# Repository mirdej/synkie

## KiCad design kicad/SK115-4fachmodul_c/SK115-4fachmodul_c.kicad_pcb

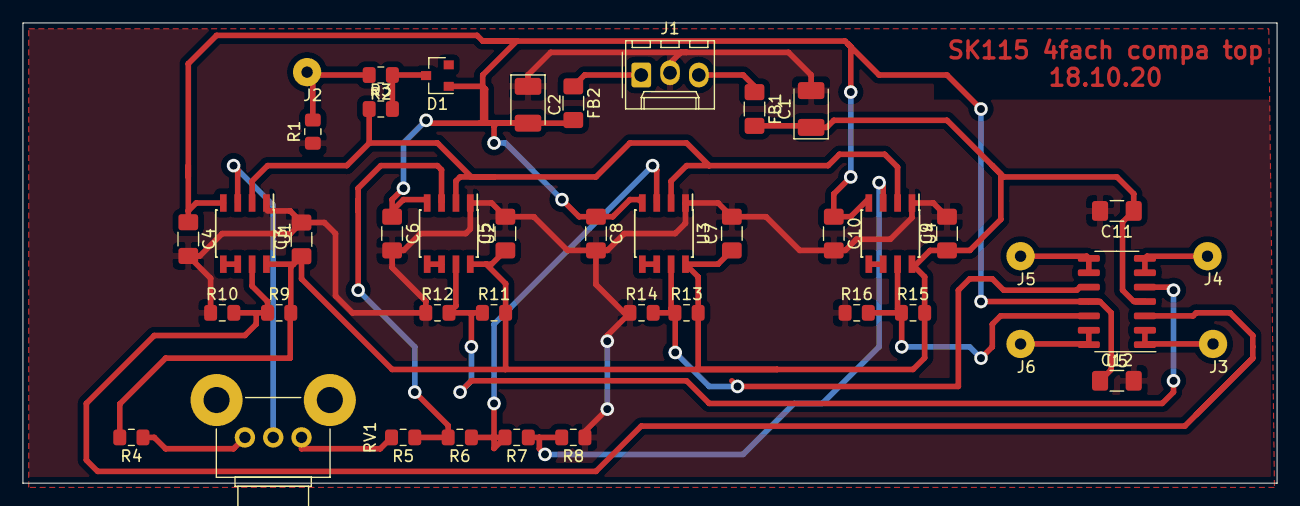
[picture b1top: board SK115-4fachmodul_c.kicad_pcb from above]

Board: 2 copper layers, 110.7 x 40.6 mm, 43 parts (0 on the bottom side), 25 nets.

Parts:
C1, C2: 10u; CP_EIA-3528-21_Kemet-B_Pad1.50x2.35mm_HandSolder
C3, C4, C5, C6, C7, C8, C9, C10, C11, C12: 100n; C_1206_3216Metric_Pad1.42x1.75mm_HandSolder
D1: BAT54S; SOT-23
FB1, FB2: 330u; L_1206_3216Metric_Pad1.42x1.75mm_HandSolder
J1: Power; Molex_KK-254_AE-6410-03A_1x03_P2.54mm_Vertical
J2: SIFF_IN; Solderpad_1mm
J3: CV4; Solderpad_1mm
J4: CV3; Solderpad_1mm
J5: CV2; Solderpad_1mm
J6: CV1; Solderpad_1mm
R1: 4k7; R_0805_2012Metric_Pad1.15x1.40mm_HandSolder
R2, R3: 100; R_0805_2012Metric_Pad1.15x1.40mm_HandSolder
R4: 49k; R_0805_2012Metric_Pad1.15x1.40mm_HandSolder
R5, R6, R7, R8: 2k2; R_0805_2012Metric_Pad1.15x1.40mm_HandSolder
R9, R11, R13, R15: 6k8; R_0805_2012Metric_Pad1.15x1.40mm_HandSolder
R10, R12, R14, R16: 1k8; R_0805_2012Metric_Pad1.15x1.40mm_HandSolder
RV1: 10k; Potentiometer_Alps_RK09K_Single_Horizontal
U1, U2, U3, U4: LM311D; SOIC-8_3.9x4.9mm_P1.27mm
U5: TL074; SOIC-14_3.9x8.7mm_P1.27mm

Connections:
+5V: C1.1, C3.1, C5.1, C7.1, C9.1, C11.1, D1.2, FB1.2, R4.2, R9.2, R11.2, R13.2, R15.2, U1.8, U2.8, U3.8, U4.8, U5.4
-5V: C2.2, C4.1, C6.1, C8.1, C10.1, C12.1, D1.1, FB2.2, U1.4, U2.4, U3.4, U4.4, U5.11
GND: C1.2, C2.1, C3.2, C4.2, C5.2, C6.2, C7.2, C8.2, C9.2, C10.2, C11.2, C12.2, J1.2, R1.1, R8.1, R10.1, R12.1, R14.1, R16.1, U1.1, U2.1, U3.1, U4.1
unnamed: D1.3, R2.1, R3.2
unnamed: FB1.1, J1.3
unnamed: FB2.1, J1.1
unnamed: J2.1, R1.2, R2.2
unnamed: J3.1, U5.1, U5.2
unnamed: J4.1, U5.6, U5.7
unnamed: J5.1, U5.8, U5.9
unnamed: J6.1, U5.13, U5.14
unnamed: R3.1, U1.2, U2.2, U3.2, U4.2
unnamed: R4.1, RV1.1
unnamed: R5.1, R6.2, U2.3
unnamed: R5.2, RV1.2, RV1.3, U1.3
unnamed: R6.1, R7.2, U3.3
unnamed: R7.1, R8.2, U4.3
unnamed: R9.1, R10.2, U1.7, U5.3
unnamed: R11.1, R12.2, U2.7, U5.5
unnamed: R13.1, R14.2, U3.7, U5.10
unnamed: R15.1, R16.2, U4.7, U5.12
unnamed: U1.5, U1.6
unnamed: U2.5, U2.6
unnamed: U3.5, U3.6
unnamed: U4.5, U4.6

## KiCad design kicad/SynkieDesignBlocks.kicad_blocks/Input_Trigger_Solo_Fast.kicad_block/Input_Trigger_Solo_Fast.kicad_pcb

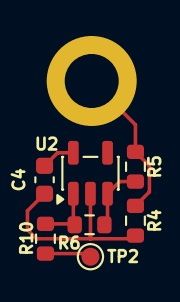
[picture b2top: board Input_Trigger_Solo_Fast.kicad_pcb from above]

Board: 2 copper layers, 8 parts (1 on the bottom side), 6 nets.

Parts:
C4: 100n; C_0603_1608Metric
J3: Clock In; Banana2mm-Löthülse
R4: 12k; R_0603_1608Metric
R5: 2k2; R_0603_1608Metric
R6: 100k; R_0603_1608Metric
R10: 75; R_0603_1608Metric
TP2: Comp2Out; TestPoint_Pad_D1.0mm
U2: TLV3201; SOT-23-5

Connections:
+5V: C4.2, U2.5 (V+)
GND: C4.1, R4.1, U2.2 (V-)
unnamed: J3.1 (Pin_1_1), R4.2, R5.2
unnamed: R6.1, R10.2, U2.1
unnamed: R5.1, R6.2, U2.3 (+)
unnamed: R10.1, TP2.1 (1_1)

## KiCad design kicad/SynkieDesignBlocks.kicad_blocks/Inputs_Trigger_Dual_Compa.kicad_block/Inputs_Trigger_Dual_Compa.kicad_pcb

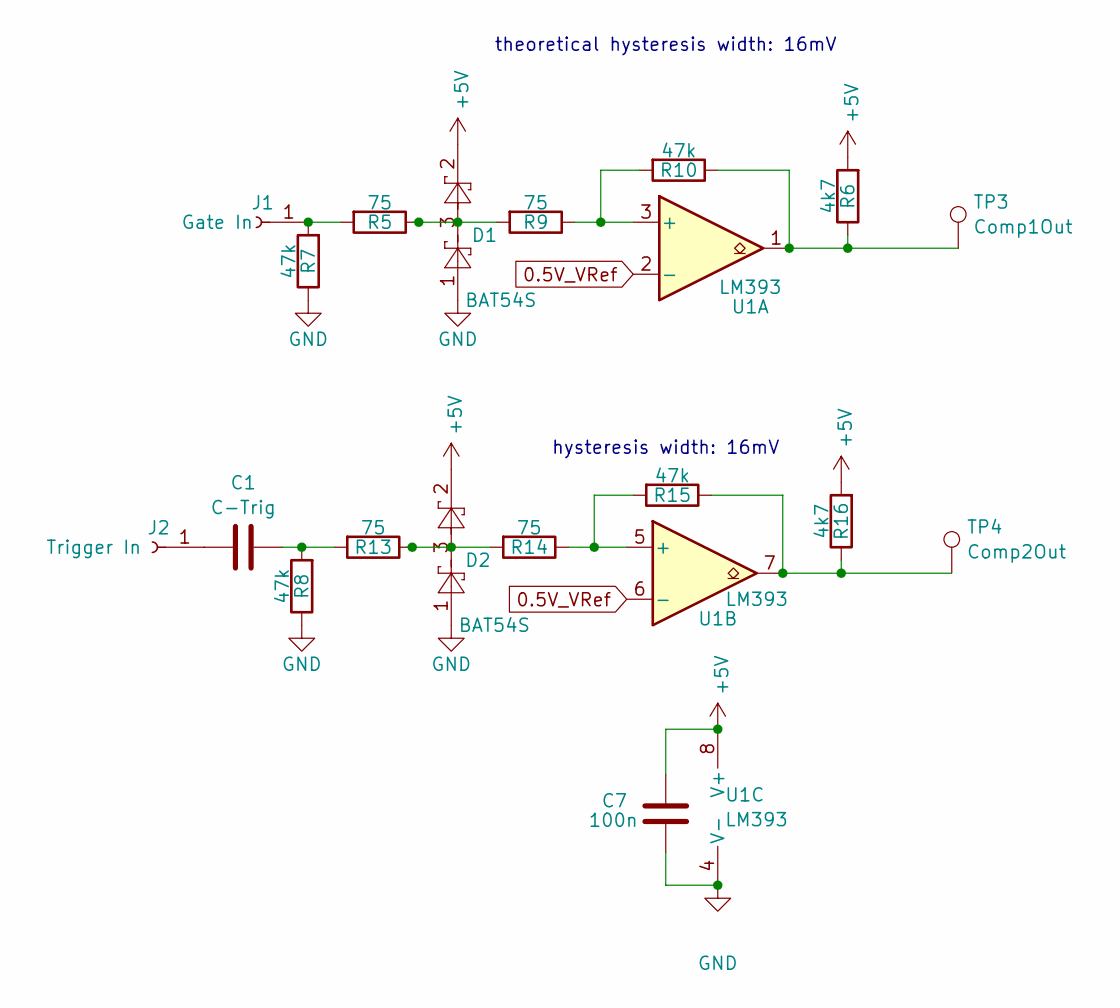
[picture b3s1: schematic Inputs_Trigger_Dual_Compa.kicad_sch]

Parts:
C1: C-Trig; C_0805_2012Metric
C7: 100n; C_0603_1608Metric; LCSC C14663
D1, D2: BAT54S; SOT-23; LCSC C8592
J1: Gate In; Banana2mm-Löthülse
J2: Trigger In; Banana2mm-Löthülse
R5, R9, R13, R14: 75; R_0603_1608Metric; LCSC C4275
R6, R16: 4k7; R_0603_1608Metric; LCSC C23162
R7, R8, R10, R15: 47k; R_0603_1608Metric; LCSC C25819
TP3: Comp1Out; TestPoint_Pad_D1.0mm
TP4: Comp2Out; TestPoint_Pad_D1.0mm
U1: LM393; SOIC-8_3.9x4.9mm_P1.27mm; LCSC C7955

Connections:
0.5V_VRef: U1.2 (-), U1.6 (-)
+5V: C7.1, D1.2, D2.2, R6.2, R16.2, U1.8 (V+)
GND: C7.2, D1.1, D2.1, R7.1, R8.1, U1.4 (V-)
unnamed: C1.2, R8.2, R13.2
unnamed: D1.3, R5.1, R9.2
unnamed: D2.3, R13.1, R14.2
unnamed: J1.1 (Pin_1_1), R5.2, R7.2
unnamed: C1.1, J2.1 (Pin_1_1)
unnamed: R6.1, R10.1, TP3.1 (1_1), U1.1
unnamed: R15.1, R16.1, TP4.1 (1_1), U1.7
unnamed: R9.1, R10.2, U1.3 (+)
unnamed: R14.1, R15.2, U1.5 (+)

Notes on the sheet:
hysteresis width: 16mV
theoretical hysteresis width: 16mV

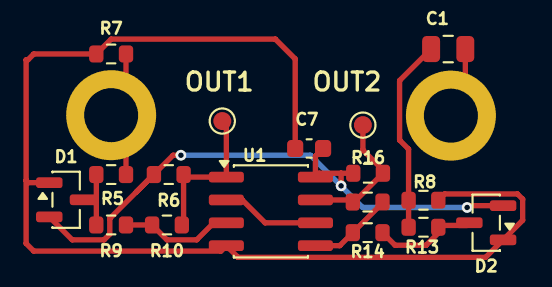
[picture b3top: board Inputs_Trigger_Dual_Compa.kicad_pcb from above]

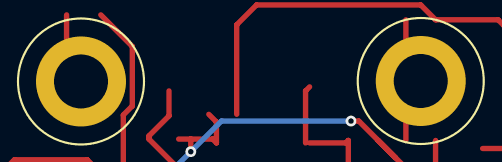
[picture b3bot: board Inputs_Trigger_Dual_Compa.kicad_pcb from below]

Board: 2 copper layers, 19 parts (2 on the bottom side), 12 nets.

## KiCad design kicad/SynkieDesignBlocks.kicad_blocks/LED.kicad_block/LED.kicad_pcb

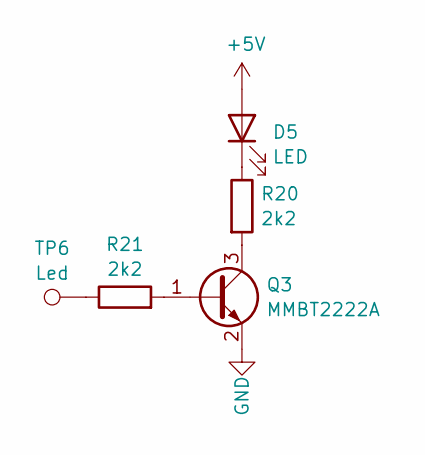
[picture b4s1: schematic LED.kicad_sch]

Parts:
D5: LED; LED_1206_3216Metric_ReverseMount_Hole1.8x2.4mm; LCSC C125108
Q3: MMBT2222A; SOT-23; LCSC C8512
R20, R21: 2k2; R_0603_1608Metric; LCSC C4190
TP6: Led; TestPoint_Pad_D1.0mm

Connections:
+5V: D5.2 (A)
GND: Q3.2 (E)
unnamed: D5.1 (K), R20.1
unnamed: Q3.1 (B), R21.2
unnamed: Q3.3 (C), R20.2
unnamed: R21.1, TP6.1 (1_1)

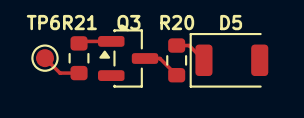
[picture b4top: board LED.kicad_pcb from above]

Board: 2 copper layers, 5 parts (0 on the bottom side), 4 nets.

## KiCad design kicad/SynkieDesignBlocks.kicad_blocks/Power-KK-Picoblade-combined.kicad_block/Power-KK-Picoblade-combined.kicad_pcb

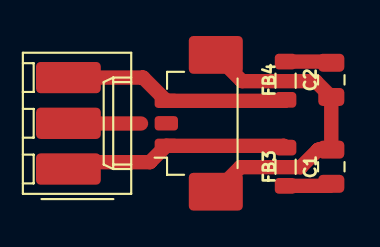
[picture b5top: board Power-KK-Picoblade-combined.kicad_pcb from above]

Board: 2 copper layers, 6 parts (0 on the bottom side), 5 nets.

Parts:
C1, C2: 10u; C_0805_2012Metric
FB3, FB4: Ferrite_Bead; L_0805_2012Metric
J1: Conn_01x03; Molex_PicoBlade_53398-0371_1x03-1MP_P1.25mm_Vertical
J2: Power; Molex_KK-254_AE-6410-03A_1x03_P2.54mm_Vertical_SMD

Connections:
+5V: C1.1, FB3.2
-5V: C2.2, FB4.2
GND: C1.2, C2.1, J1.2, J1.MP, J2.2
unnamed: FB3.1, J1.1, J2.1
unnamed: FB4.1, J1.3, J2.3

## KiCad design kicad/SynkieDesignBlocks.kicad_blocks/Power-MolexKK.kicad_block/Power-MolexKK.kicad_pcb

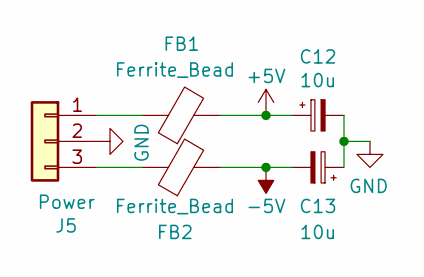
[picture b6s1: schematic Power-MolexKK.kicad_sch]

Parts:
C12, C13: 10u; C_0805_2012Metric; LCSC C15850
FB1, FB2: Ferrite_Bead; L_0805_2012Metric; LCSC C1017
J5: Power; Molex_KK-254_AE-6410-03A_1x03_P2.54mm_Vertical_SMD

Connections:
+5V: C12.1, FB1.2
-5V: C13.2, FB2.2
GND: C12.2, C13.1, J5.2
unnamed: FB1.1, J5.1
unnamed: FB2.1, J5.3

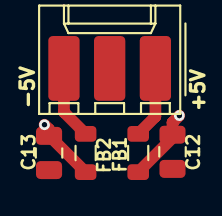
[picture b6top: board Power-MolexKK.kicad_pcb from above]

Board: 2 copper layers, 5 parts (0 on the bottom side), 5 nets.

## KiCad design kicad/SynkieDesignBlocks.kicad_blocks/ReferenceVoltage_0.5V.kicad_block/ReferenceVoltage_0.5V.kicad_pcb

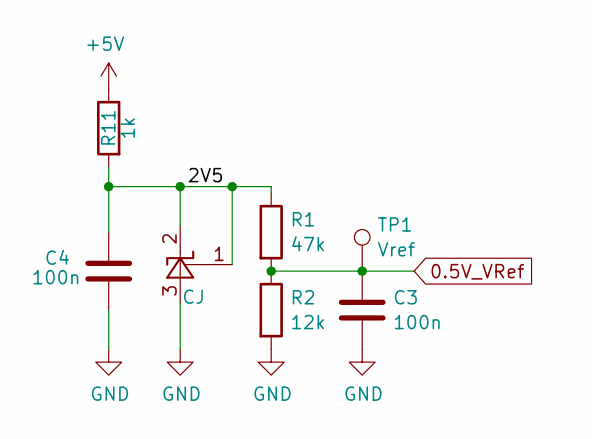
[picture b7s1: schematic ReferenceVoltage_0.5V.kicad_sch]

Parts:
C3, C4: 100n; C_0603_1608Metric; LCSC C14663
R1: 47k; R_0603_1608Metric; LCSC C25819
R2: 12k; R_0603_1608Metric; LCSC C22790
R11: 1k; R_0603_1608Metric; LCSC C21190
TP1: Vref; TestPoint_Pad_D1.0mm
U4: CJ; SOT-23; LCSC C3113

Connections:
0.5V_VRef: C3.1, R1.2, R2.1, TP1.1 (1_1)
+5V: R11.1
/2V5: C4.1, R1.1, R11.2, U4.1 (R), U4.2 (K)
GND: C3.2, C4.2, R2.2, U4.3 (A)

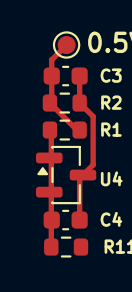
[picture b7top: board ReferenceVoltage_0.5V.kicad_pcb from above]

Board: 2 copper layers, 7 parts (0 on the bottom side), 3 nets.

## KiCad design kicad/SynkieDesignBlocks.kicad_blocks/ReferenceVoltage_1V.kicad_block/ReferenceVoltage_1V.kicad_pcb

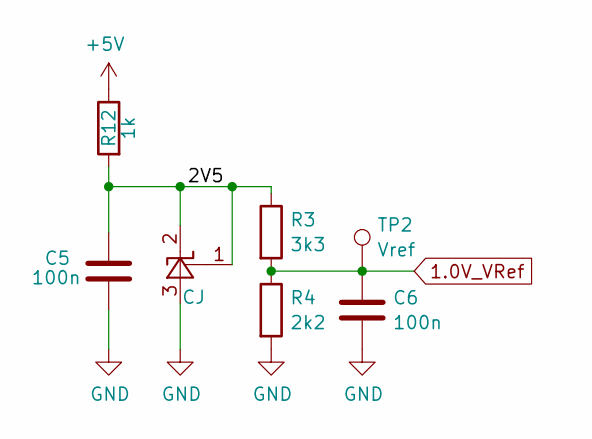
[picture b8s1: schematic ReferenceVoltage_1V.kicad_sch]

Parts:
C5, C6: 100n; C_0603_1608Metric; LCSC C14663
R3: 3k3; R_0603_1608Metric; LCSC C22978
R4: 2k2; R_0603_1608Metric; LCSC C4190
R12: 1k; R_0603_1608Metric; LCSC C21190
TP2: Vref; TestPoint_Pad_D1.0mm
U5: CJ; SOT-23; LCSC C3113

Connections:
1.0V_VRef: C6.1, R3.2, R4.1, TP2.1 (1_1)
+5V: R12.1
/2V5: C5.1, R3.1, R12.2, U5.1 (R), U5.2 (K)
GND: C5.2, C6.2, R4.2, U5.3 (A)

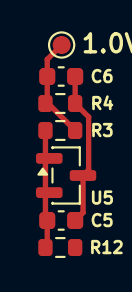
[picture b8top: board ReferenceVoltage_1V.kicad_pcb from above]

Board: 2 copper layers, 7 parts (0 on the bottom side), 3 nets.
